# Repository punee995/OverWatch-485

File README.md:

# OverWatch-485!

Project **OverWatch** initially created for GUVNL R&D Department to Monitor Modbus 3-phase meters over LoRaWAN (IN865). Hardware is developed under KiCAD5. Firmware was written under CoIDE.

## Hardware Specification

 - [x] Universal Input Voltage ( 85VAC - 265VAC )
 - [x] Input surge Voltage protection ( 2000V )
 - [x] Modbus Galvenic Isolation ( 2500V )
 - [x] U.fl Antenna / SMA Antenna / PCB Antenna ( 3dbi* )
 - [x] Protocol : RS422 / RS485 ( 500kbps )
 - [x] Internal Battery / Charger
 - [ ] Reduced Power Consumption

## Software Specification
1.  Add the AT command, the command list is shown below;
2.  Modify the time of sending data, and modify it to send a packet of data for 60s;
3.  Integrate all frequency bands, support band switching, and switch frequency bands by AT command;

     AT command list: \
     at+region=EU868/US915/AS923/AU915/IN865/KR920    // Set device region
     
     at+dev_eui=xxxxxxxxxxxxxxxx                      //  Set device dev_eui  \
     at+app_eui=xxxxxxxxxxxxxxxx                      // Set device app_eui  \
     at+app_key=xxxxxxxxxxxxxxxxxxxxxxxxxxxxxxxx      //  Set device app_key 

     at+dev_addr=xxxxxxxx                             // Set device dev_addr \
     at+nwks_key=xxxxxxxxxxxxxxxxxxxxxxxxxxxxxxxx     //  Set device nwks_key  \
     at+apps_key=xxxxxxxxxxxxxxxxxxxxxxxxxxxxxxxx     // Set device apps_key  

     at+join_mode=otaa/abp                            // Set the device to join otaa or abp \

     (Note:Please set the region first, then set the join method.)  \
     After the parameter setting is completed, reset the device enable parameter.

# TODO

## Hardware

 - [ ] Reduce Power Consumption (Currently ~45mA ).
	 - For this Add mosfet to Modbus transreciver.
 - [ ] Add Switch for Device Function as Maseter/Slave.
 - [ ] Protection Devices such as MOV and Fuse(@Mains side).

## Software 

 - [ ] programming of Device over RS485(Modbus).
	 - Settings of LoRaWAN Parameters.
	 - Settings of Modbus Registers.
	 - Settings of Alarm for Alert.

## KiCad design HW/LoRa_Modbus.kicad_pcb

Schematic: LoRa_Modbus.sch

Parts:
MH1, MH2, MH3, MH4, MH5, MH6: MountingHole_Pad; MountingHole_4.3mm_M4_Pad_Via

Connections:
GND: MH1.1, MH2.1, MH3.1, MH4.1, MH5.1, MH6.1; also elsewhere on the board

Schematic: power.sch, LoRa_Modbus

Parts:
C1, C8: 1uF; C_0603
C2, C6, C7: 10uF; C_0805
C3, C5, C23: 100nF; C_0402
C4: 220uF; CP_Elec_6.3x7.7
D1: MBR120; D_SOD-123
F1: 500mA; 1206
J1: AC; TerminalBlock_bornier-2_P5.08mm
J2: BATT; JST_PH_B2B-PH-K_02x2.00mm_Straight
JP1: BAT; SMT-JUMPER_2_NO_SILK
Q1: Si2301DS; SOT-23
R1: 10k; R_0402
R2, R3, R4, R5: 100k; R_0402
TP1: +5v; Measurement_Point_Round-SMD-Pad_Small
TP2: 4V2; Measurement_Point_Round-SMD-Pad_Small
TP3: 3V3; Measurement_Point_Round-SMD-Pad_Small
U1: LTH7S; SOT-23-5
U2: HLK-PM0x; HLK-PM01
U3: SPX3819M5-L-3-3; SOT-23-5

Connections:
+3V3: C7.1, C8.1, TP3.1, U3.5 (OUT); also elsewhere on the board
+5V: C1.2, C3.1, C4.1, C6.2, D1.1, F1.1, R5.1, TP1.1, U1.4, U3.1 (IN); also elsewhere on the board
+BATT: C2.2, C23.2, D1.2, J2.1, JP1.1, Q1.3, R2.1, TP2.1, U1.3
/main/BATT_ADC: C5.1, R3.2, R4.1; also elsewhere on the board
/main/BATT_CHRG: U1.1; also elsewhere on the board
/main/BATT_EN: Q1.1, R2.2; also elsewhere on the board
GND: C1.1, C2.1, C3.2, C4.2, C5.2, C6.1, C7.2, C8.2, C23.1, J2.2, R1.2, R4.2, U1.2, U2.3, U3.2 (GND); also elsewhere on the board
unnamed: F1.2, U2.4
unnamed: J1.1, U2.1
unnamed: J1.2, U2.2
unnamed: JP1.2, Q1.2, R3.1
unnamed: R1.1, U1.5
unnamed: R5.2, U3.3 (EN)

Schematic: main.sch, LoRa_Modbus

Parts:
AE1: PCB_ANT; SWRA416
C9: 10uF; C_0805
C10, C13: 100nF; C_0402
C11, C12: NC; C_0402
D2: LED_RAGB
J3: DBG; Pin_Header_Straight_2x06_Pitch2.54mm_SMD
J$1: ANTENNATINY; SMA_UFL_PAD_TINY
L1: NC; L_0402
R6, R8, R9, R10, R11, R12, R13, R14: 10k; R_0402
R7: 100k; R_0402
R15, R16, R17: 1k; R_0402
SW1: SW_Push; SW_SPST_PTS645
U4: RAK811; RAK811_MODULE

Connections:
+3V3: C9.1, C10.1, D2.2, J3.2, R6.1, R7.1, R8.1, R9.1, R10.1, R11.1, R12.1, R13.1, R14.1, U4.11; also elsewhere on the board
+5V: J3.1; also elsewhere on the board
/RS485_RX: R9.2, U4.26; also elsewhere on the board
/RS485_TX: R10.2, U4.25; also elsewhere on the board
/RS485_~DE: U4.27; also elsewhere on the board
/main/BATT_ADC: U4.22; also elsewhere on the board
/main/BATT_CHRG: R15.2; also elsewhere on the board
/main/BATT_EN: U4.23; also elsewhere on the board
/main/BOOT0: J3.10, U4.17
/main/DBG_RX: J3.5, R6.2, U4.7
/main/DBG_TX: J3.7, R8.2, U4.6
/main/I2C_SCL: J3.8, R12.2, U4.18
/main/I2C_SDA: J3.6, R11.2, U4.19
/main/LED_BLUE: R16.2, U4.9
/main/LED_GREEN: R17.2, U4.8
/main/RST: C13.2, J3.12, R7.2, SW1.1, U4.24
/main/SWCLK: J3.11, R14.2, U4.13
/main/SWDIO: J3.9, R13.2, U4.10
GND: AE1.2, C9.2, C10.2, C11.2, C12.2, C13.1, J3.3, J3.4, J$1.GND1, J$1.GND2, J$1.GND3, J$1.GND4, SW1.2, U4.1, U4.12, U4.21, U4.28, U4.29, U4.30, U4.31, U4.32, U4.34; also elsewhere on the board
unnamed: AE1.1, C11.1, J$1.ANT1, J$1.ANT2, J$1.ANT3, L1.1
unnamed: C12.1, L1.2, U4.33
unnamed: D2.1, R15.1
unnamed: D2.3, R16.1
unnamed: D2.4, R17.1

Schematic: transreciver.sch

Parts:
C14, C16, C19, C21: 100nF; C_0402
C15, C20: 10nF; C_0402
C17, C22: 10uF; C_0805
C18: 100nF; C_1812
J4: RS485; TerminalBlock_bornier-4_P5.08mm
JP2: TR; SMT-JUMPER_2_NO_SILK
L2, L3: 2k@100Mhz; L_0805
R18: 120R; R_0402
TP4: 3V3_ISO; Measurement_Point_Round-SMD-Pad_Small
U5: ADM2587E; SOIC-20W_7.5x12.8mm_Pitch1.27mm

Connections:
+3.3VADC: C19.1, C20.1, C21.1, C22.1, L2.1, L2.2, TP4.1, U5.12, U5.19
+3V3: C14.1, C15.1, C16.1, C17.1, U5.2, U5.8; also elsewhere on the board
/RS485_RX: U5.4; also elsewhere on the board
/RS485_TX: U5.7; also elsewhere on the board
/RS485_~DE: U5.5, U5.6; also elsewhere on the board
/transreciver/A+: J4.1, JP2.1, U5.18
/transreciver/A-: J4.2, R18.1, U5.17
/transreciver/B+: J4.3, U5.13
/transreciver/B-: J4.4, U5.15
GND: C14.2, C15.2, C16.2, C17.2, C18.2, U5.1, U5.3, U5.9, U5.10; also elsewhere on the board
GNDPWR: C18.1, C19.2, C20.2, C21.2, C22.2, L3.1, L3.2, U5.11, U5.14, U5.16, U5.20
unnamed: JP2.2, R18.2

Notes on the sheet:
Note :Place near Pin 1,2
Note :Place near Pin 8,9,10
Note :Place near Pin 19,20
Note :Place near Pin 11,12

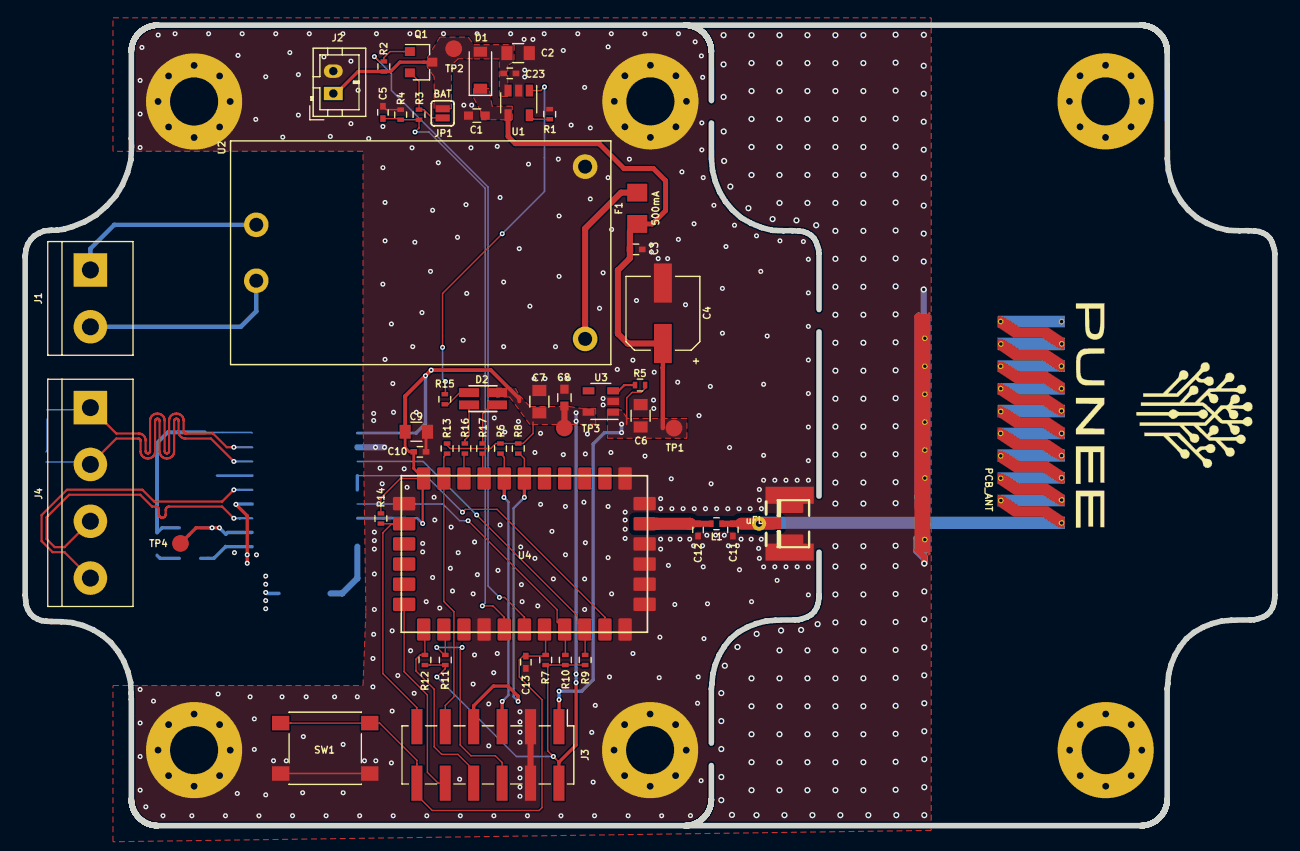
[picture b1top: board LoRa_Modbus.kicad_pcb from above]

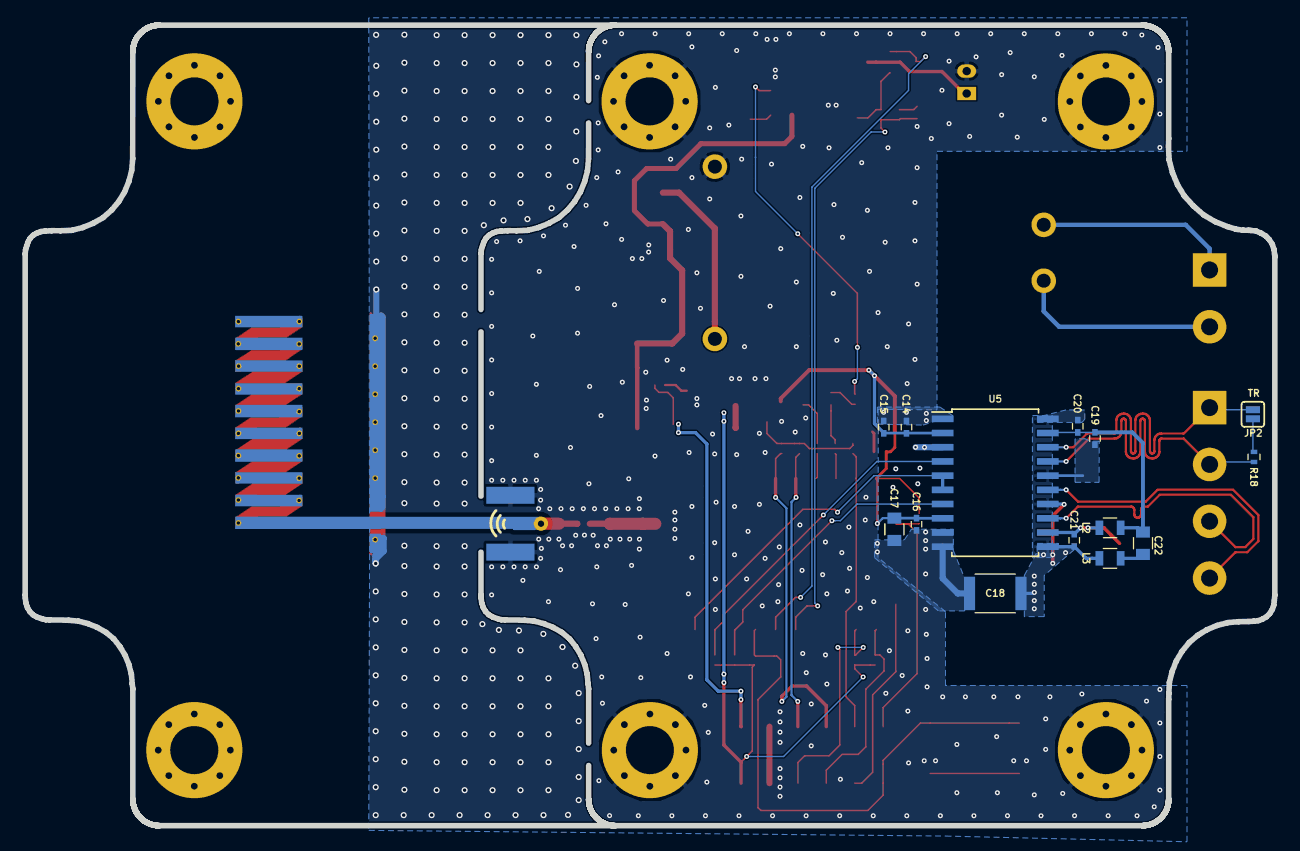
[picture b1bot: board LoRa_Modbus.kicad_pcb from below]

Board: 2 copper layers, 111.7 x 71.6 mm, 72 parts (15 on the bottom side), 38 nets.

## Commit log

2020-09-09 Update README.md
    Updated TODO
2020-09-09 Update README.md
    Update README.md
2020-09-09 Create LICENSE
2020-09-09 Added Images
